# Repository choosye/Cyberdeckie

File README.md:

# Cyberdeckie
Half Life Hack Club Week 5 - Cyberdeckie

## What it is 
A clamshell handheld Linux terminal built around a Raspberry Pi Zero 2 W, with a 3.5" screen, a 40-key keyboard and its own rechargeable battery. Made for Hack Club Half Life, Week 5. 

## Features
- Raspberry Pi Zero 2 W running Linux, mounted like a HAT on a 2×20 socket
- 3.5" ST7796 IPS display (480×320) over SPI, connected by a 14-pin FPC cable
- 40-key (4×10) matrix keyboard with a diode on every key
- USB-C charging with power-path (it can run while charging)
- 1S LiPo battery boosted to a steady 5 V
- Power slide switch + safe-shutdown button
- 3 status LEDs (charging, USB connected, power)
- Serial debug header for when the screen/keyboard aren't working yet

## PCB

## How it works

Power: USB-C (5.1k CC resistors) → BQ24074 charger/power-path → VSYS → TPS61023 boost → +5 V for the Pi and display. The slide switch controls the boost converter's EN pin.

Display: SPI0 (MOSI, SCLK, CE0) plus DC, RST and a backlight PWM pin. The module has its own backlight transistor.

Keyboard: 4 rows × 10 columns on GPIOs, active-low, with 1N4148W diodes (cathode toward the column) so pressing multiple keys doesn't cause ghosting.

Shutdown button: on GPIO3, which can both trigger a safe shutdown and wake the Pi (dtoverlay=gpio-shutdown).

Serial debug (J1): UART TX/RX/GND for a USB-serial adapter.

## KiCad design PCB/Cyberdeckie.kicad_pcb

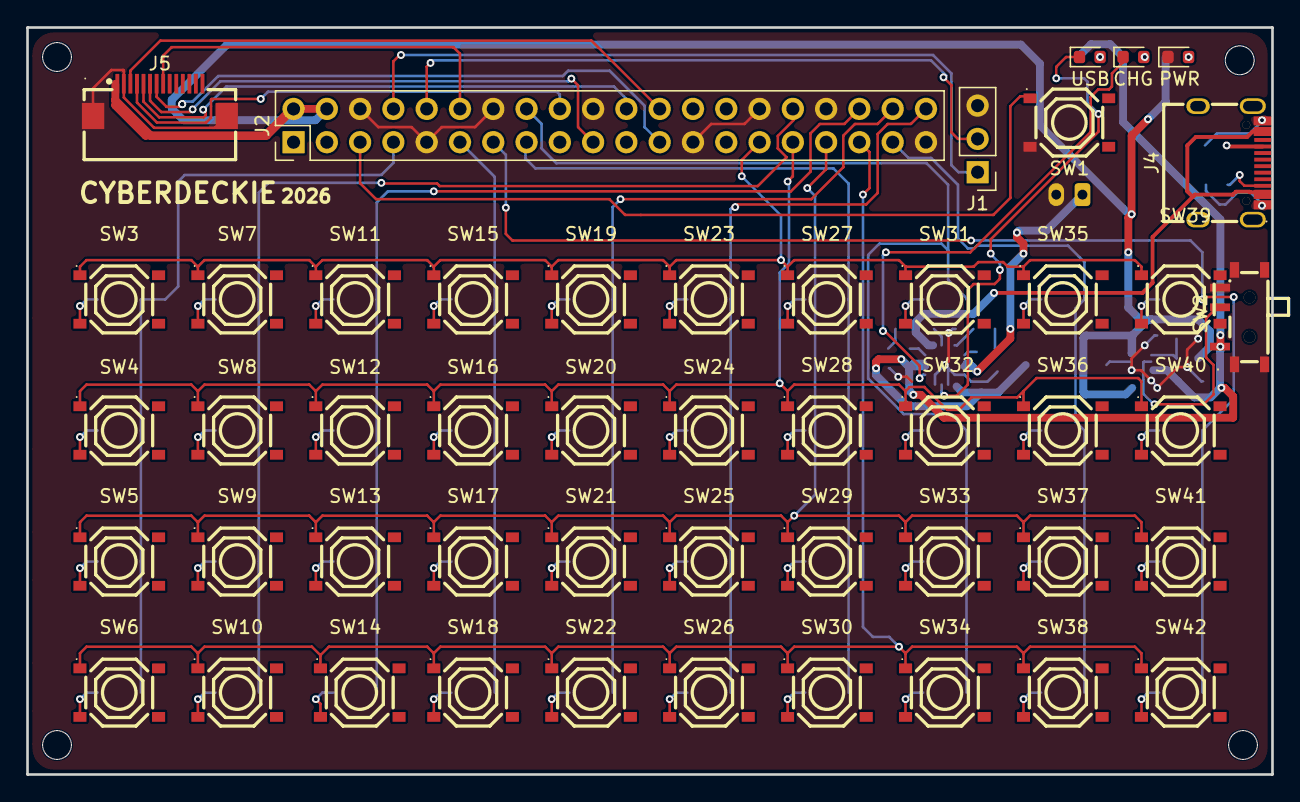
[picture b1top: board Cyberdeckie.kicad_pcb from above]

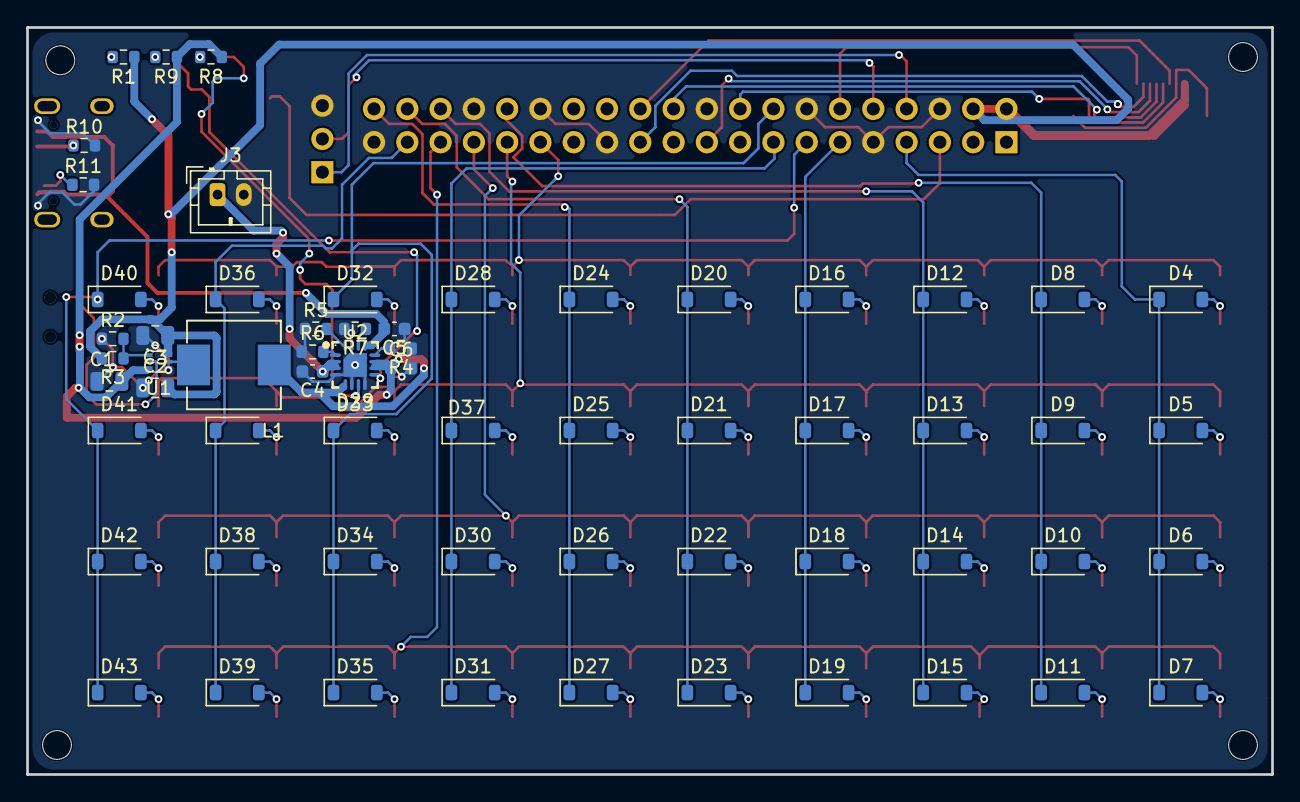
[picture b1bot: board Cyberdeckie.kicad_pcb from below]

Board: 2 copper layers, 95.0 x 57.0 mm, 110 parts (61 on the bottom side), 82 nets.

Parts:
C1: 10uF; C_0805_2012Metric
C2, C3: 22uF; C_0805_2012Metric
C4, C6: 4.7uF; C_0603_1608Metric
C5: 1uF; C_0603_1608Metric
D1, D2, D3: LED; LED_0603_1608Metric
D4, D5, D6, D7, D8, D9, D10, D11, D12, D13, D14, D15, D16, D17, D18, D19, D20, D21, D22, D23, D24, D25, D26, D27, D28, D29, D30, D31, D32, D33, D34, D35, D36, D37, D38, D39, D40, D41, D42, D43: D; D_SOD-123
J1: Serial Debug; PinHeader_1x03_P2.54mm_Vertical
J2: Raspberry_Pi_Zero_2_W; PinHeader_2x20_P2.54mm_Vertical
J3: Battery (JST-PH); JST_PH_B2B-PH-K_1x02_P2.00mm_Vertical
J4: TYPE-C-31-M-12; USB-C_SMD-TYPE-C-31-M-12_1
J5: ST7796 3.5in Display (FPC); FPC-SMD_14P-P0.50_DEALON_FC05-S14FCT-00
L1: 1uH; IND-SMD_L7.3-W6.6_MHCI06030
R1: 1k; R_0603_1608Metric
R2: 100k; R_0603_1608Metric
R3: 732k; R_0603_1608Metric
R4: 1.18k; R_0603_1608Metric
R5: 1.13k; R_0603_1608Metric
R6: 10k; R_0603_1608Metric
R7: 46.4k; R_0603_1608Metric
R8, R9: 1.5k; R_0603_1608Metric
R10, R11: 5.1; R_0603_1608Metric
SW1, SW3, SW4, SW5, SW6, SW7, SW8, SW9, SW10, SW11, SW12, SW13, SW14, SW15, SW16, SW17, SW18, SW19, SW20, SW21, SW22, SW23, SW24, SW25, SW26, SW27, SW28, SW29, SW30, SW31, SW32, SW33, SW34, SW35, SW36, SW37, SW38, SW39, SW40, SW41, SW42: TS-1187A-B-A-B; SW-SMD_4P-L5.1-W5.1-P3.70-LS6.5-TL_H1.5
SW2: MSK12C02; SW-TH_MSK12C02
U1: TPS61023DRLR; SOT-563_L1.6-W1.2-P0.50-LS1.6-BR
U2: BQ24074RGTR; QFN-16_L3.0-W3.0-P0.50-TL-EP1.7

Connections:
+5V: C2.2, C3.1, J2.2 (5V), J2.4 (5V), J5.1, R1.1, R3.2, U1.6 (VOUT)
COL0: D4.1 (K), D5.1 (K), D6.1 (K), D7.1 (K), J2.7 (GCLK0/GPIO4)
COL1: D8.1 (K), D9.1 (K), D10.1 (K), D11.1 (K), J2.32 (PWM0/GPIO12)
COL2: D12.1 (K), D13.1 (K), D14.1 (K), D15.1 (K), J2.36 (GPIO16)
COL3: D16.1 (K), D17.1 (K), D18.1 (K), D19.1 (K), J2.11 (GPIO17)
COL4: D20.1 (K), D21.1 (K), D22.1 (K), D23.1 (K), J2.38 (GPIO20/MOSI1)
COL5: D24.1 (K), D25.1 (K), D26.1 (K), D27.1 (K), J2.40 (GPIO21/SCLK1)
COL6: D28.1 (K), D29.1 (K), D30.1 (K), D31.1 (K), J2.15 (GPIO22)
COL7: D32.1 (K), D33.1 (K), D34.1 (K), D35.1 (K), J2.16 (GPIO23)
COL8: D36.1 (K), D37.1 (K), D38.1 (K), D39.1 (K), J2.37 (GPIO26)
COL9: D40.1 (K), D41.1 (K), D42.1 (K), D43.1 (K), J2.13 (GPIO27)
GND: C1.1, C2.1, C3.2, C4.2, C5.1, C6.2, D1.1 (K), J1.3, J2.6 (GND), J2.9 (GND), J2.14 (GND), J2.20 (GND), J2.25 (GND), J2.30 (GND), J2.34 (GND), J2.39 (GND), J3.2, J4.A1B12 (GND), J4.B1A12 (GND), J5.2, J5.15, J5.16, R2.1, R4.1, R5.1, R6.1, R7.2, R10.2, R11.2, SW1.3 (C), SW2.3, SW2.4, U1.4 (GND), U2.4 (~CE), U2.6 (EN1), U2.8 (VSS), U2.17 (EP)
LCD_BL: J2.12 (GPIO18/PWM0), J5.8
LCD_CS: J2.24 (~CE0/GPIO8), J5.3
LCD_DC: J2.22 (GPIO25), J5.5
LCD_MOSI: J2.19 (MOSI0/GPIO10), J5.6
LCD_RST: J2.18 (GPIO24), J5.4
LCD_SCK: J2.23 (SCLK0/GPIO11), J5.7
unnamed: D1.2 (A), R1.2
unnamed: D2.2 (A), R8.1
unnamed: D2.1 (K), U2.7 (~PGOOD)
unnamed: D3.2 (A), R9.1
unnamed: D3.1 (K), U2.9 (~CHG)
unnamed: D4.2 (A), SW3.3 (C)
unnamed: D5.2 (A), SW4.3 (C)
unnamed: D6.2 (A), SW5.3 (C)
unnamed: D7.2 (A), SW6.3 (C)
unnamed: D8.2 (A), SW7.3 (C)
unnamed: D9.2 (A), SW8.3 (C)
unnamed: D10.2 (A), SW9.3 (C)
unnamed: D11.2 (A), SW10.3 (C)
unnamed: D12.2 (A), SW11.3 (C)
unnamed: D13.2 (A), SW12.3 (C)
unnamed: D14.2 (A), SW13.3 (C)
unnamed: D15.2 (A), SW14.3 (C)
unnamed: D16.2 (A), SW15.3 (C)
unnamed: D17.2 (A), SW16.3 (C)
unnamed: D18.2 (A), SW17.3 (C)
unnamed: D19.2 (A), SW18.3 (C)
unnamed: D20.2 (A), SW19.3 (C)
unnamed: D21.2 (A), SW20.3 (C)
unnamed: D22.2 (A), SW21.3 (C)
unnamed: D23.2 (A), SW22.3 (C)
unnamed: D24.2 (A), SW23.3 (C)
unnamed: D25.2 (A), SW24.3 (C)
unnamed: D26.2 (A), SW25.3 (C)
unnamed: D27.2 (A), SW26.3 (C)
unnamed: D28.2 (A), SW27.3 (C)
unnamed: D29.2 (A), SW28.3 (C)
unnamed: D30.2 (A), SW29.3 (C)
unnamed: D31.2 (A), SW30.3 (C)
unnamed: D32.2 (A), SW31.3 (C)
unnamed: D33.2 (A), SW32.3 (C)
unnamed: D34.2 (A), SW33.3 (C)
unnamed: D35.2 (A), SW34.3 (C)
unnamed: D36.2 (A), SW35.3 (C)
unnamed: D37.2 (A), SW36.3 (C)
unnamed: D38.2 (A), SW37.3 (C)
unnamed: D39.2 (A), SW38.3 (C)
unnamed: D40.2 (A), SW39.3 (C)
unnamed: D41.2 (A), SW40.3 (C)
unnamed: D42.2 (A), SW41.3 (C)
unnamed: D43.2 (A), SW42.3 (C)
unnamed: J4.A5 (CC1), R10.1
unnamed: J4.B5 (CC2), R11.1
unnamed: SW2.2, U1.2 (EN)
unnamed: R2.2, R3.1, U1.1 (FB)
unnamed: L1.2, U1.5 (SW)
unnamed: R4.2, U2.12 (ILIM)
unnamed: R5.2, U2.16 (ISET)
unnamed: R7.1, U2.14 (TMR)
unnamed: R6.2, U2.1 (TS)
ROW0: J2.29 (GCLK1/GPIO5), SW3.1 (A), SW7.1 (A), SW11.1 (A), SW15.1 (A), SW19.1 (A), SW23.1 (A), SW27.1 (A), SW31.1 (A), SW35.1 (A), SW39.1 (A)
ROW1: J2.31 (GCLK2/GPIO6), SW4.1 (A), SW8.1 (A), SW12.1 (A), SW16.1 (A), SW20.1 (A), SW24.1 (A), SW28.1 (A), SW32.1 (A), SW36.1 (A), SW40.1 (A)
ROW2: J2.33 (PWM1/GPIO13), SW5.1 (A), SW9.1 (A), SW13.1 (A), SW17.1 (A), SW21.1 (A), SW25.1 (A), SW29.1 (A), SW33.1 (A), SW37.1 (A), SW41.1 (A)
ROW3: J2.35 (GPIO19/MISO1), SW6.1 (A), SW10.1 (A), SW14.1 (A), SW18.1 (A), SW22.1 (A), SW26.1 (A), SW30.1 (A), SW34.1 (A), SW38.1 (A), SW42.1 (A)
SHUTDOWN: J2.5 (SCL/GPIO3), SW1.1 (A)
UART_RX: J1.2, J2.10 (GPIO15/RXD)
UART_TX: J1.1, J2.8 (GPIO14/TXD)
VBAT: C4.1, J3.1, U2.2 (BAT), U2.3 (BAT)
VBUS: C5.2, J4.A4B9 (VBUS), J4.B4A9 (VBUS), U2.13 (IN)
VSYS: C1.2, C6.1, L1.1, R8.2, R9.2, SW2.1, U1.3 (VIN), U2.5 (EN2), U2.10 (OUT), U2.11 (OUT)
